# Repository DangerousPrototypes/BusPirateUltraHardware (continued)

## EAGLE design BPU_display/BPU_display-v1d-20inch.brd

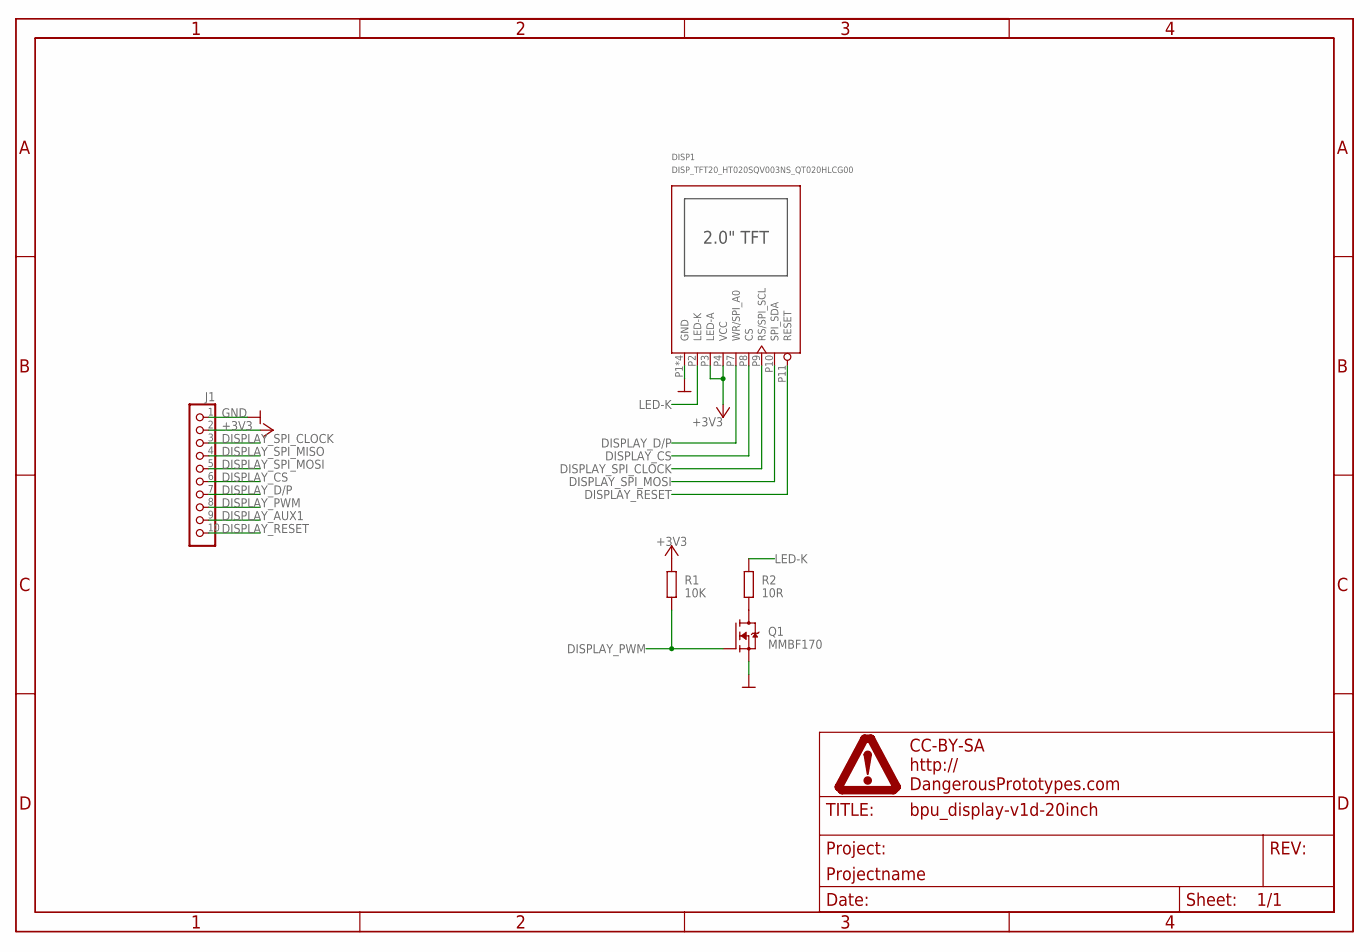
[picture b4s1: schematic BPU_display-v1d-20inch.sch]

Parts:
DISP1: DISP_TFT20_HT020SQV003NS_QT020HLCG00; HT020SQV003NS_QT020HLCG00
J1: CON-FPC_X05B20L10T; X05B20L10T
PAGE1: FRAME_DINA4_L; DP_LOGO
Q1: MMBF170; SOT-23
R1: 10K; R0603
R2: 10R; R0603

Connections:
+3V3: DISP1.P3 (LED-A), DISP1.P4 (VCC), J1.2, R1.2
DISPLAY_AUX1: J1.9
DISPLAY_CS: DISP1.P8 (CS), J1.6
DISPLAY_D/P: DISP1.P7 (WR/SPI_A0), J1.7
DISPLAY_PWM: J1.8, Q1.1 (G), R1.1
DISPLAY_RESET: DISP1.P11 (RESET), J1.10
DISPLAY_SPI_CLOCK: DISP1.P9 (RS/SPI_SCL), J1.3
DISPLAY_SPI_MISO: J1.4
DISPLAY_SPI_MOSI: DISP1.P10 (SPI_SDA), J1.5
GND: DISP1.P1 (GND), DISP1.P5 (GND), DISP1.P6 (GND), DISP1.P12 (GND), J1.1, Q1.2 (S)
LED-K: DISP1.P2 (LED-K), R2.2
unnamed: Q1.3 (D), R2.1

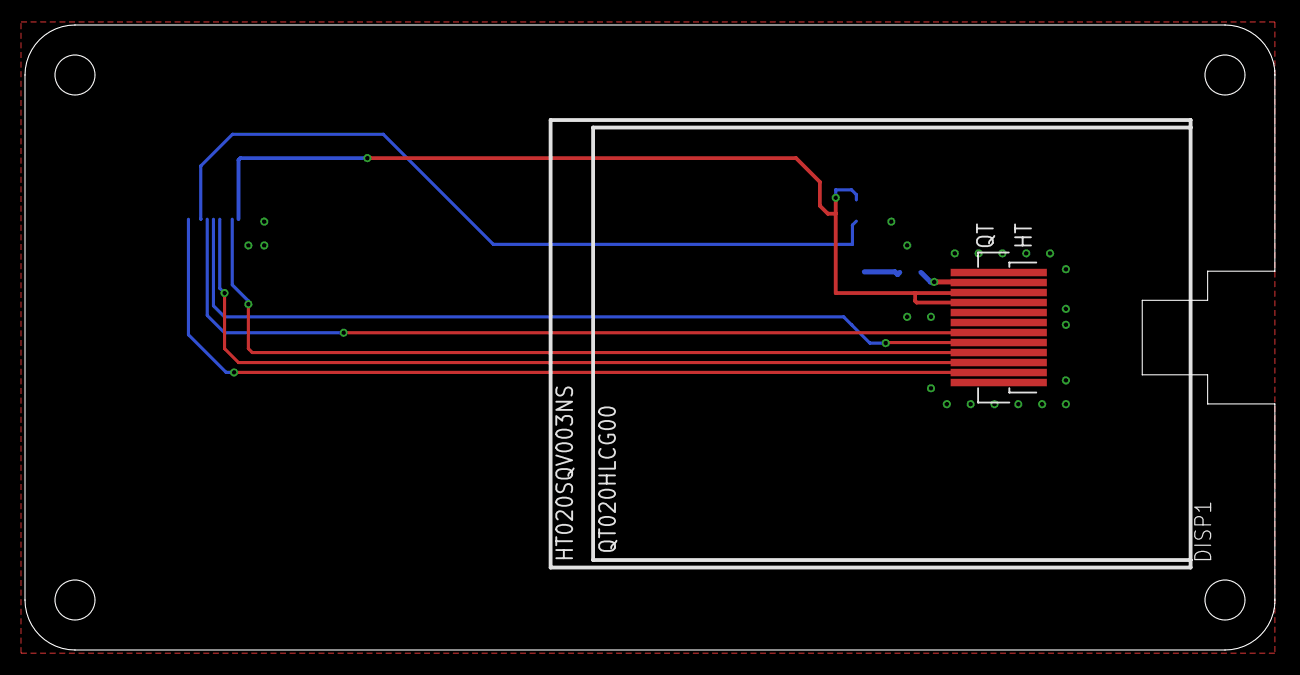
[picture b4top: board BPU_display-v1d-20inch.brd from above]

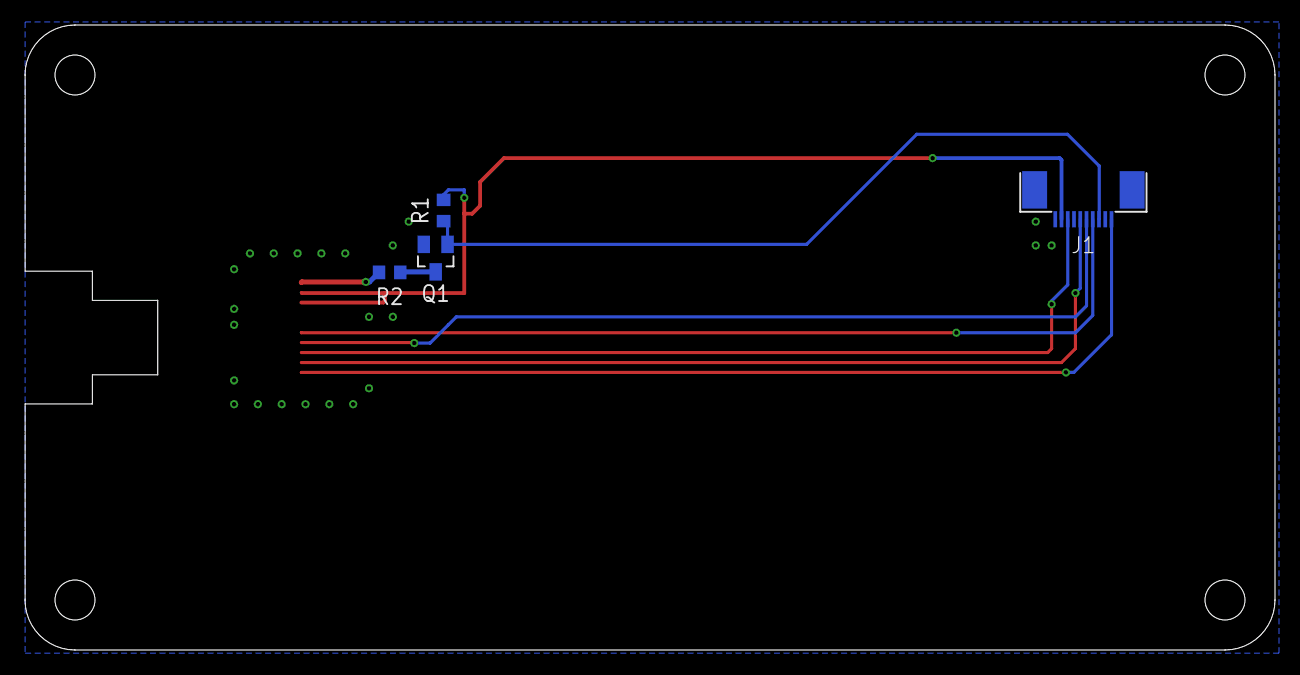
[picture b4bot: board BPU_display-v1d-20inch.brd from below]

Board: 2 copper layers, 100.0 x 50.0 mm, 6 parts (4 on the bottom side), 10 nets.

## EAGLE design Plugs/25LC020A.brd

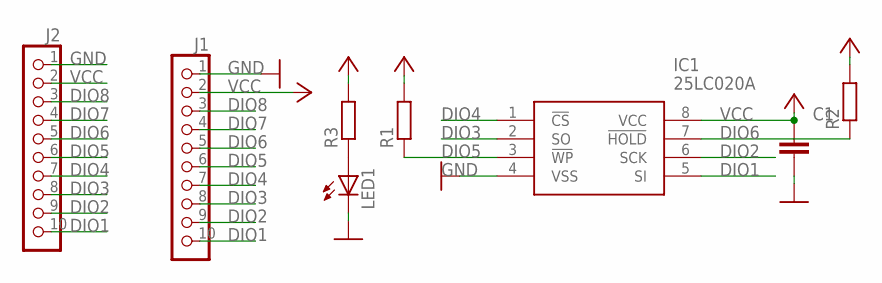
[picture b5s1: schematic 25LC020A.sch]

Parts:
C1: CAPACITOR_NPOL-0603; C603
IC1: 25LC020A; SOIC127P600X175-8N
J1: CON_HEADER_1X10-RIGHT_ANGLED_PTH; M1X10_FEMALE_RIGHT_ANGLED_PTH
J2: CON_HEADER_1X10-PTH; M1X10
LED1: LED-0805; LED-805
R1, R2, R3: RESISTOR-0603; R603

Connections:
DIO1: IC1.5 (SI), J1.10, J2.10
DIO2: IC1.6 (SCK), J1.9, J2.9
DIO3: IC1.2 (SO), J1.8, J2.8
DIO4: IC1.1 (!CS), J1.7, J2.7
DIO5: IC1.3 (!WP), J1.6, J2.6, R1.1
DIO6: IC1.7 (!HOLD), J1.5, J2.5, R2.1
DIO7: J1.4, J2.4
DIO8: J1.3, J2.3
GND: C1.2, IC1.4 (VSS), J1.1, J2.1, LED1.C
unnamed: LED1.A, R3.1
VCC: C1.1, IC1.8 (VCC), J1.2, J2.2, R1.2, R2.2, R3.2

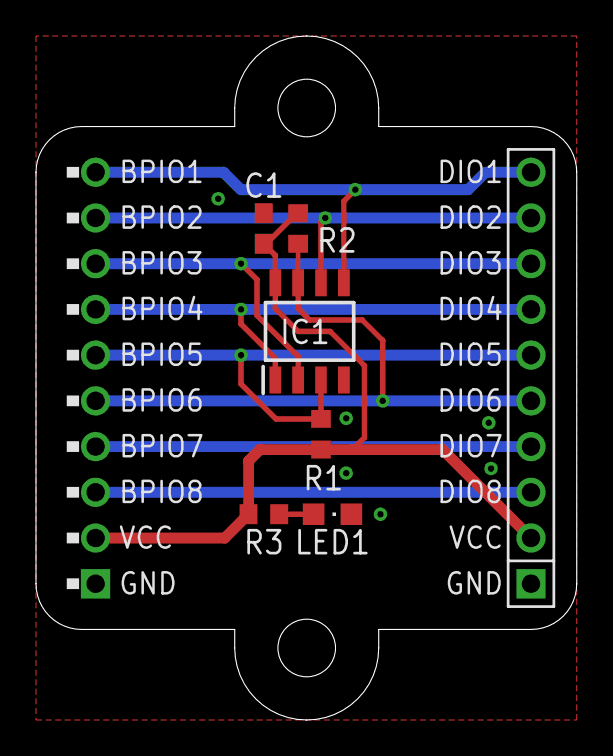
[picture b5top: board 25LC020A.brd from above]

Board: 2 copper layers, 30.0 x 38.0 mm, 8 parts (0 on the bottom side), 11 nets.

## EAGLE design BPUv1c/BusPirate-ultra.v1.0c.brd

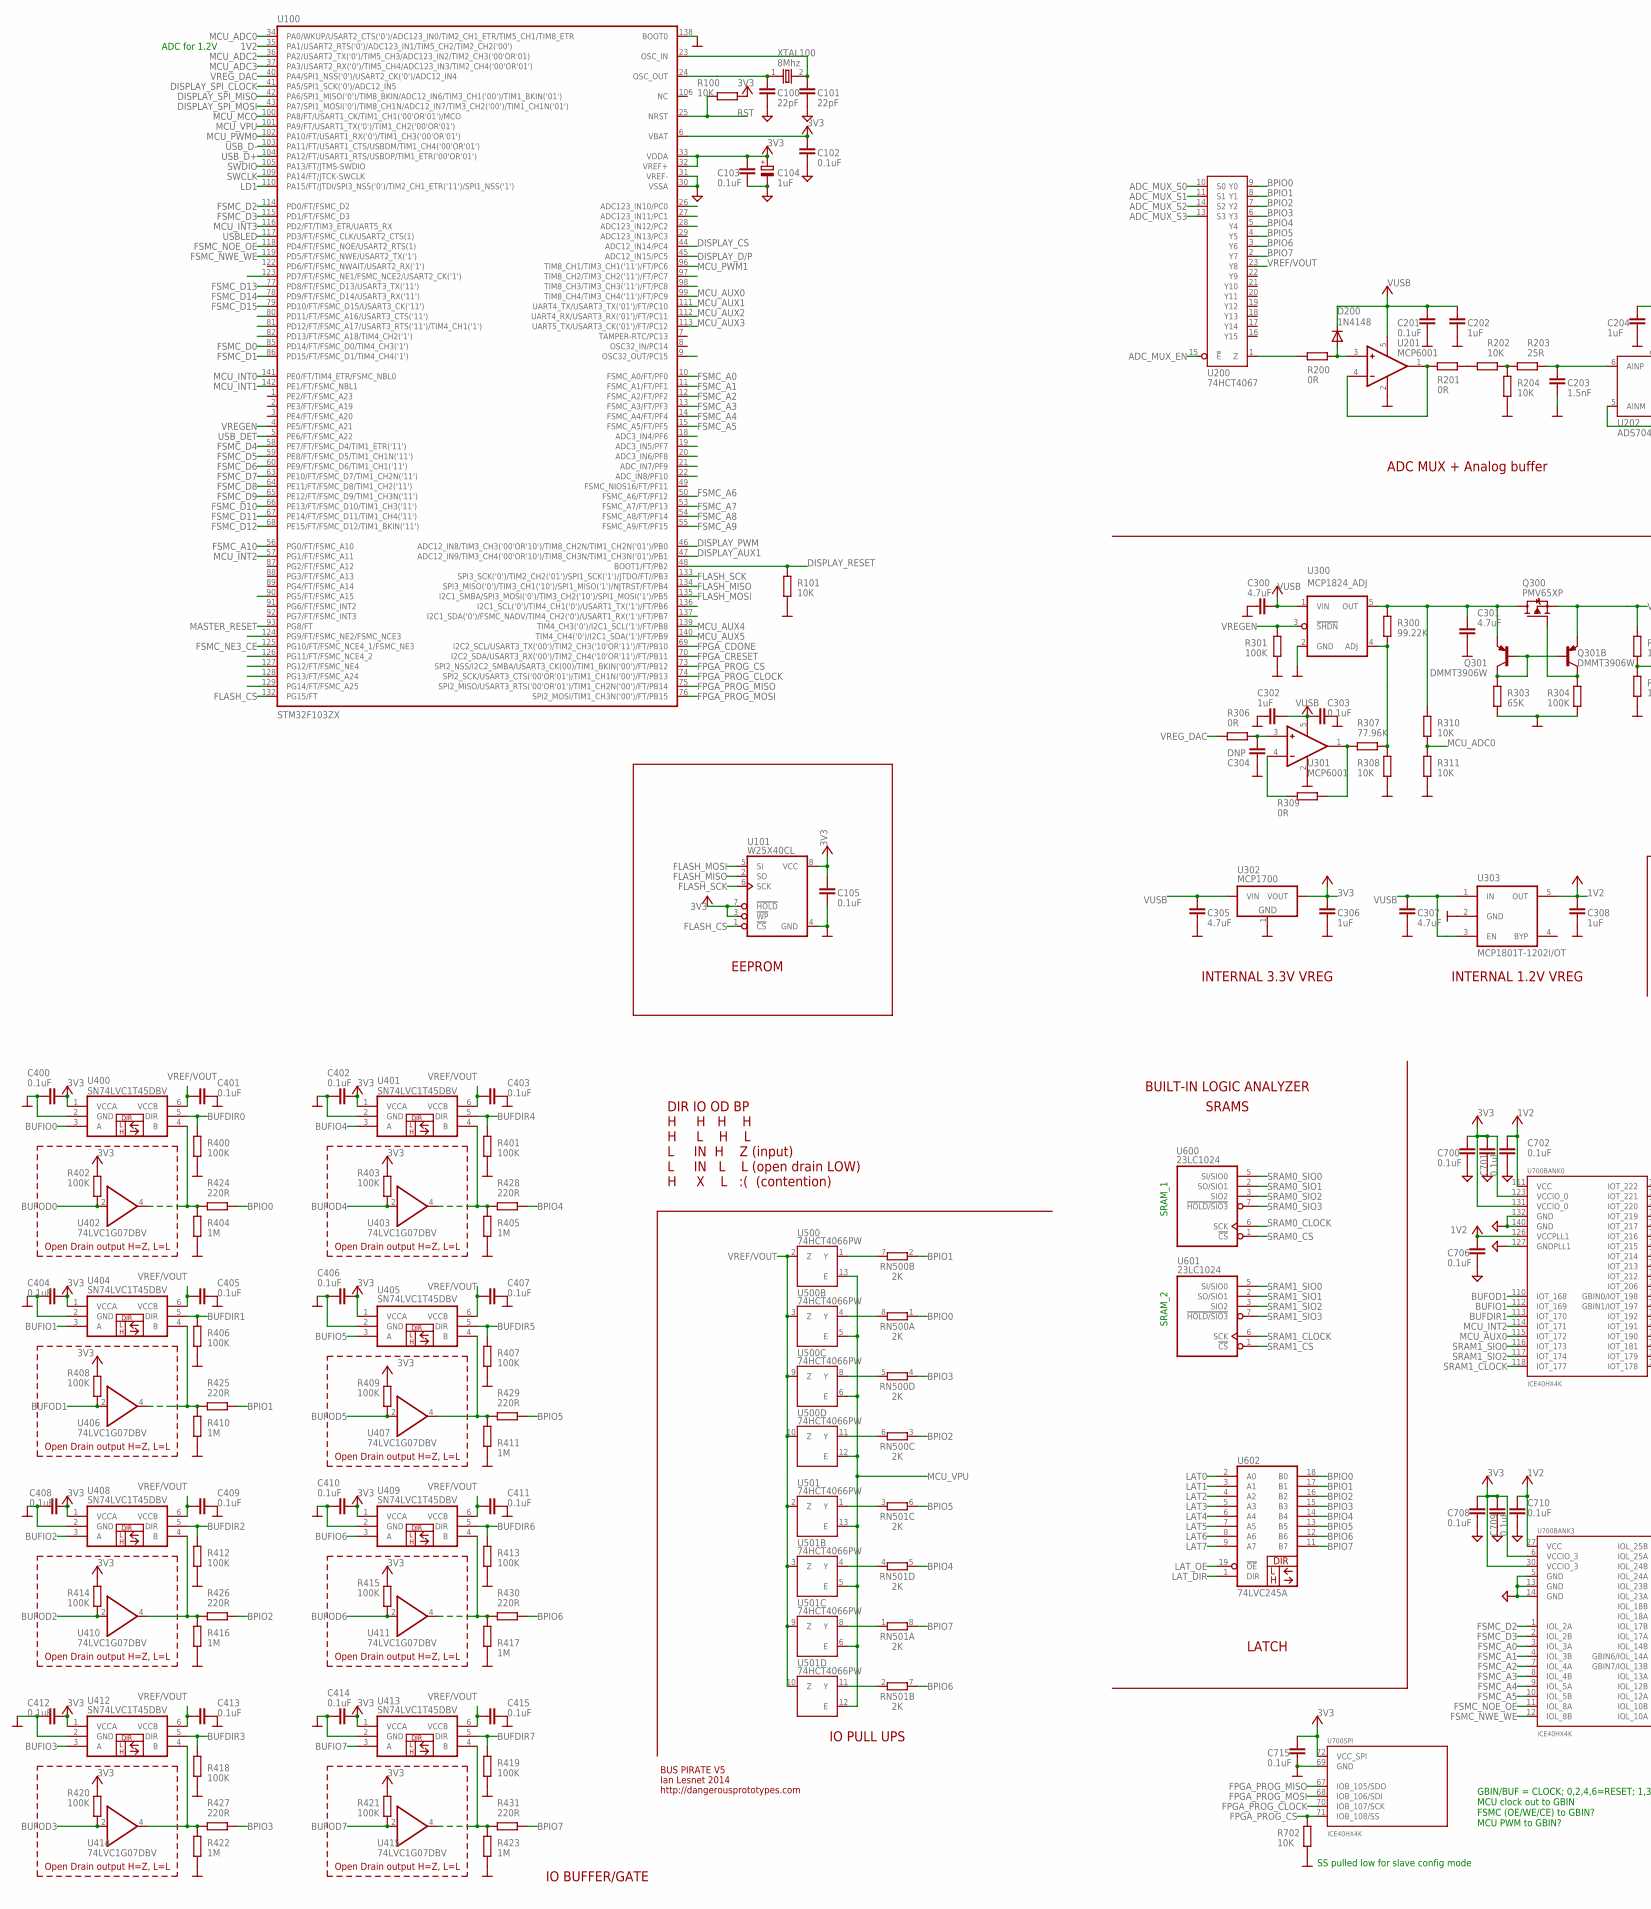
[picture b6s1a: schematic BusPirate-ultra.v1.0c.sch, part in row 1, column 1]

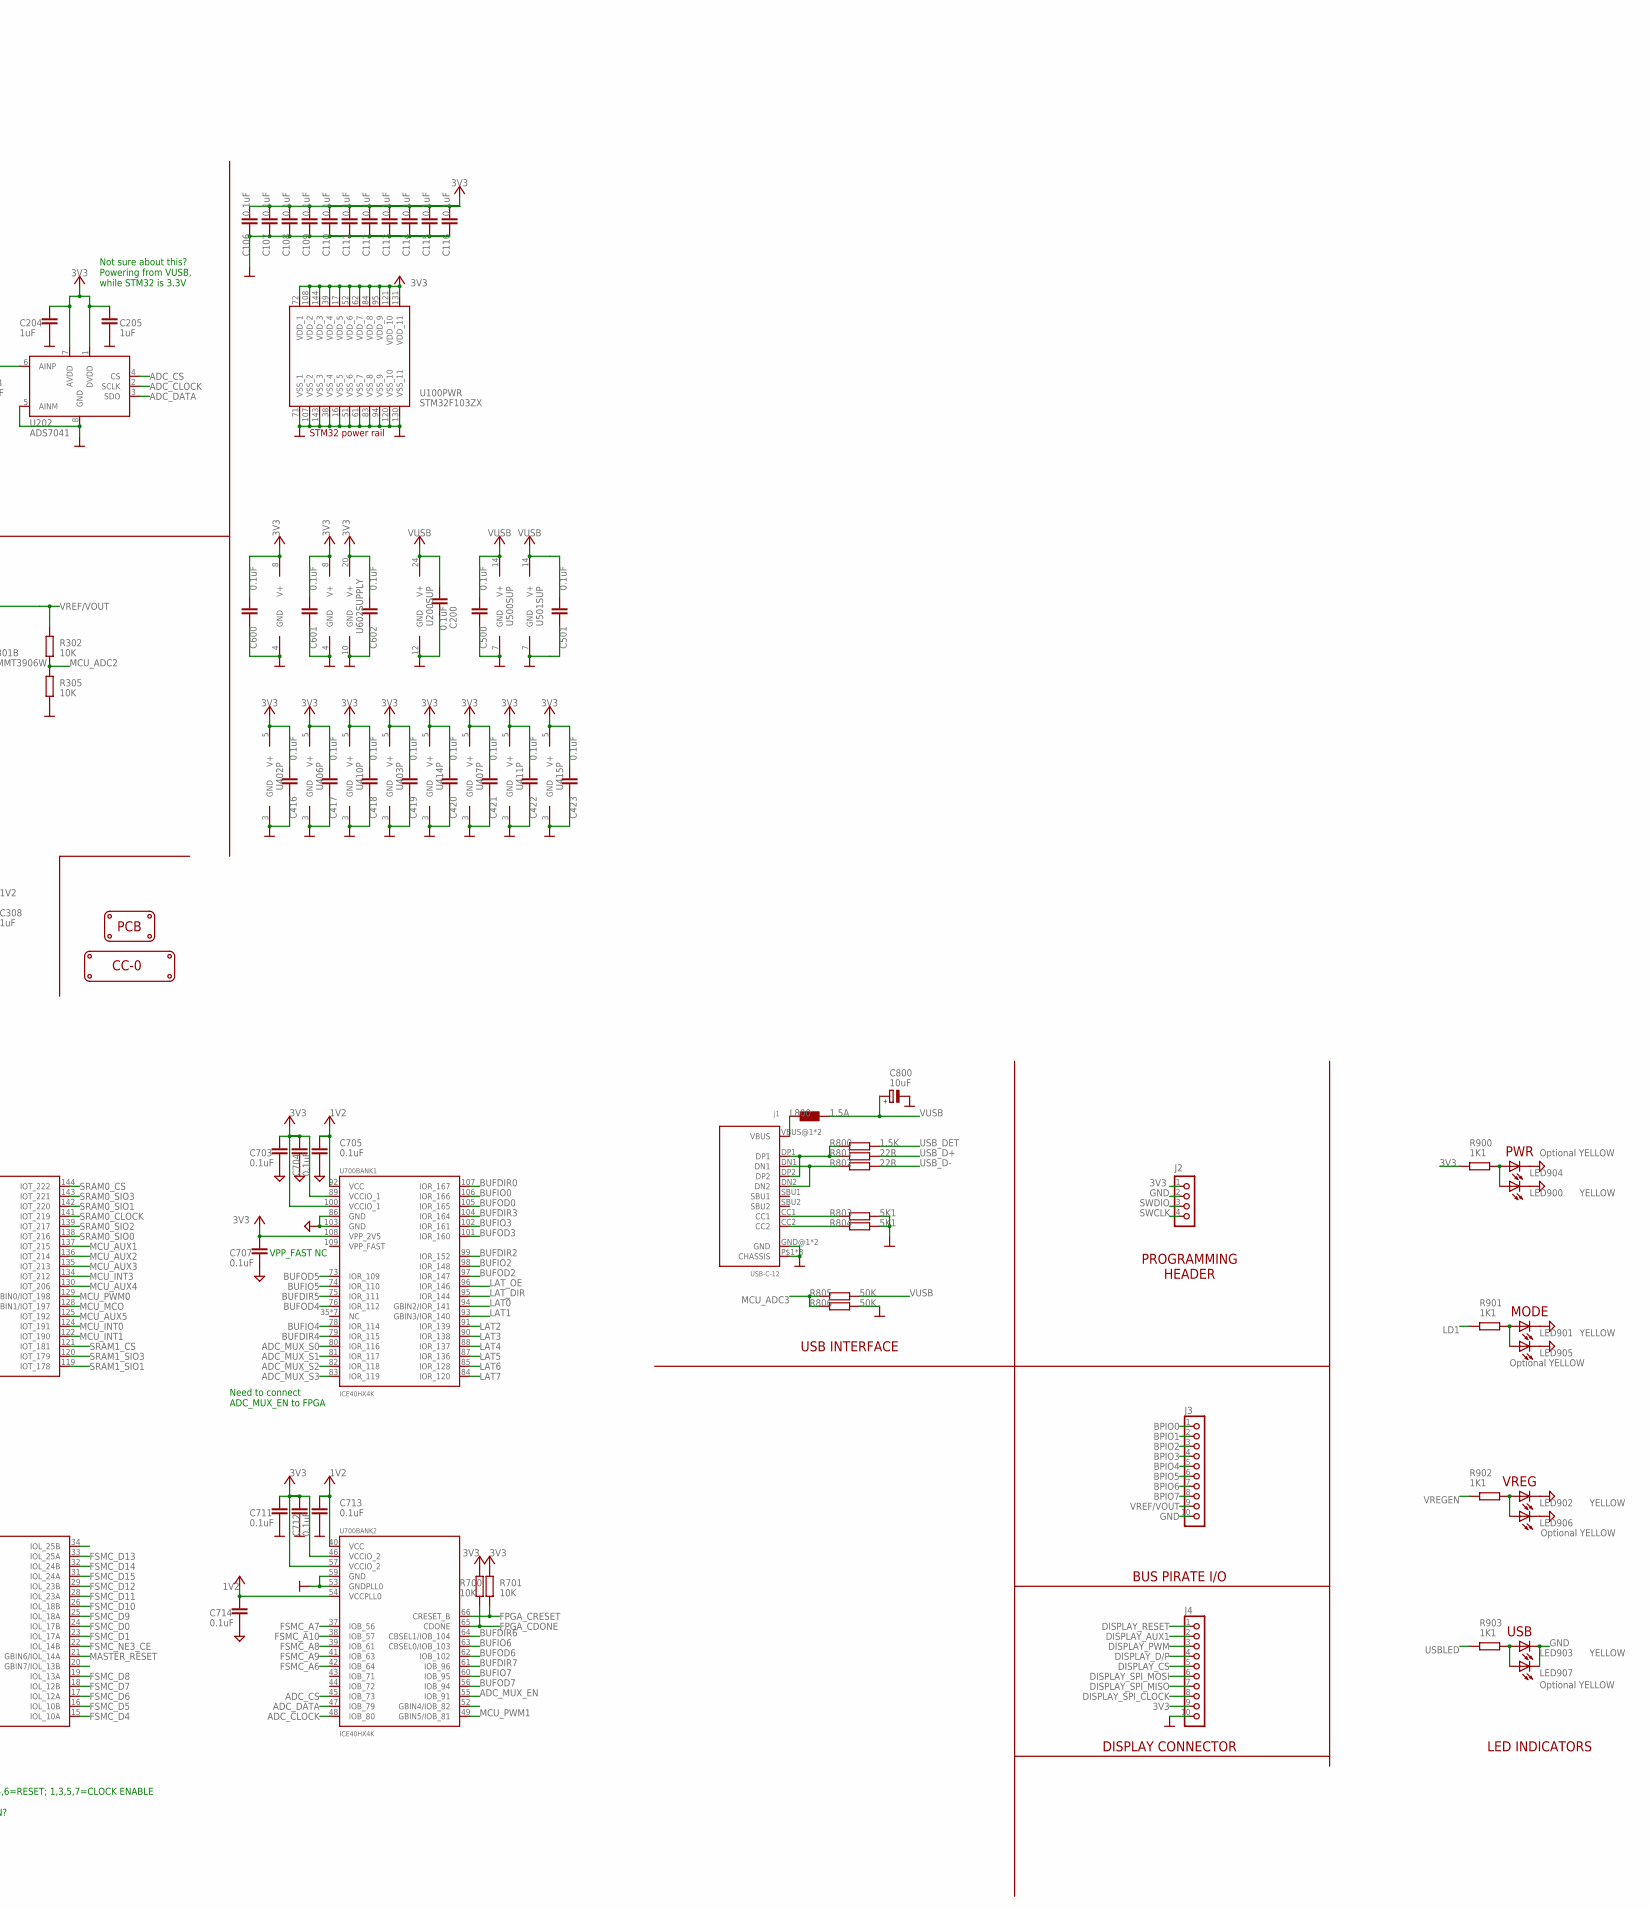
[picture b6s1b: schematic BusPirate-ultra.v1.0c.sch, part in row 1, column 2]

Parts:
C100, C101: 22pF; C402
C102, C103, C106, C108, C109, C110, C111, C112, C113, C114, C200, C201, C303, C400, C401, C402, C403, C404, C405, C406, C407, C408, C409, C410, C411, C412, C413, C414, C415, C416, C417, C418, C419, C420, C421, C422, C423, C501, C602, C702, C703, C704, C705, C707, C708, C709, C710, C711, C712, C713, C714, C715: 0.1uF; C402
C104: 1uF; SMC_A
C105, C107, C115, C116, C500, C600, C601, C700, C701, C706: 0.1uF; C603
C202, C204, C205, C302, C308: 1uF; C402
C203: 1.5nF; C402
C300, C301, C305, C307: 4.7uF; C603
C304: DNP; C603
C306: 1uF; C603
C800: 10uF; SMC_A
D200: 1N4148; SOD-123
J1: USB-C-12; C-31-M-12
J2: CON_HEADER_1X04; M1X4
J3: CON_HEADER_1X10-RIGHT_ANGLED_PTH_SHROUDED; M1X10_MALE_RIGHT_ANGLES_PTH_SHROUDED
J4: CON-FPC_X05B20L10T; X05B20L10T
L800: 1.5A; WE-KI_0805_B
LED900, LED901, LED902, LED903: YELLOW; LED-805
LED904, LED905, LED906, LED907: Optional YELLOW; LED-805
LOGO1: LOGO_CC-0
PCB1: PCB_DP_RECTANGLE-50X100; DP10050_V1
Q300: PMV65XP; SOT-23
Q301: DMMT3906W; SOT-363
R100, R101, R202, R204, R308, R310, R311, R700, R701, R702: 10K; R402
R200, R201, R309: 0R; R402
R203: 25R; R402
R300: 99.22K; R402
R301, R400, R401, R402, R403, R406, R407, R408, R409, R412, R413, R414, R415, R418, R419, R420, R421: 100K; R402
R302, R305: 10K; R603
R303: 65K; R603
R304: 100K; R603
R306: 0R; R603
R307: 77.96K; R402
R404, R405, R410, R411, R416, R417, R422, R423: 1M; R402
R424, R425, R426, R427, R428, R429, R430, R431: 220R; R402
R800: 1.5K; R402
R801, R802: 22R; R402
R803, R804: 5K1; R402
R805, R806: 50K; R402
R900, R901, R902, R903: 1K1; R603
RN500, RN501: 2K; RN8P-4R-CRA06S
U100: STM32F103ZX; TQFP-144
U101: W25X40CL; SOIC-8
U200: 74HCT4067; TSSOP-24
U201, U301: MCP6001; SOT-23-5
U202: ADS7041; VSSOP-8_DCU_PDSO_G8
U300: MCP1824_ADJ; SOT-23-5
U302: MCP1700; SOT-89
U303: MCP1801T-1202I/OT; SOT-23-5@1
U400, U401, U404, U405, U408, U409, U412, U413: SN74LVC1T45DBV; SC-70-6
U402, U403, U406, U407, U410, U411, U414, U415: 74LVC1G07DBV; SC-70-5
U500, U501: 74HCT4066PW; TSSOP-14
U600, U601: 23LC1024; SOIC-8
U602: 74LVC245A; TSSOP-20
U700: ICE40HX4K; TQFP-144
XTAL100: 8Mhz; XTAL_4X6

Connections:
1V2: C308.2, C702.1, C705.1, C706.1, C710.1, C713.1, C714.1, U100.35 (PA1/USART2_RTS('0')/ADC123_IN1/TIM5_CH2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), U303.5 (OUT), U700.27 (VCC), U700.40 (VCC), U700.54 (VCCPLL0), U700.92 (VCC), U700.111 (VCC), U700.126 (VCCPLL1)
3V3: C102.1, C103.1, C104.+, C105.1, C106.1, C107.1, C108.1, C109.1, C110.1, C111.1, C112.1, C113.1, C114.1, C115.1, C116.1, C204.1, C205.1, C306.2, C400.2, C402.2, C404.2, C406.2, C408.2, C410.2, C412.2, C414.2, C416.2, C417.2, C418.2, C419.2, C420.2, C421.2, C422.2, C423.2, C600.2, C601.2, C602.2, C700.1, C701.1, C703.1, C704.1, C707.1, C708.1, C709.1, C711.1, C712.1, C715.1, J2.1, J4.9, R100.2, R402.2, R403.2, R408.2, R409.2, R414.2, R415.2, R420.2, R421.2, R700.2, R701.2, R900.2, U100.6 (VBAT), U100.17 (VDD_5), U100.32 (VREF+), U100.33 (VDDA), U100.39 (VDD_4), U100.52 (VDD_6), U100.62 (VDD_7), U100.72 (VDD_1), U100.84 (VDD_8), U100.95 (VDD_9), U100.108 (VDD_2), U100.121 (VDD_10), U100.131 (VDD_11), U100.144 (VDD_3), U101.3 (!WP), U101.7 (!HOLD), U101.8 (VCC), U202.1 (DVDD), U202.7 (AVDD), U302.3 (VOUT), U400.1 (VCCA), U401.1 (VCCA), U402.5 (V+), U403.5 (V+), U404.1 (VCCA), U405.1 (VCCA), U406.5 (V+), U407.5 (V+), U408.1 (VCCA), U409.1 (VCCA), U410.5 (V+), U411.5 (V+), U412.1 (VCCA), U413.1 (VCCA), U414.5 (V+), U415.5 (V+), U600.8 (V+), U601.8 (V+), U602.20 (V+), U700.6 (VCCIO_3), U700.30 (VCCIO_3), U700.46 (VCCIO_2), U700.57 (VCCIO_2), U700.72 (VCC_SPI), U700.89 (VCCIO_1), U700.100 (VCCIO_1), U700.108 (VPP_2V5), U700.123 (VCCIO_0), U700.131 (VCCIO_0)
ADC_CLOCK: U202.2 (SCLK), U700.48 (IOB_80)
ADC_CS: U202.4 (CS), U700.45 (IOB_73)
ADC_DATA: U202.3 (SDO), U700.47 (IOB_79)
ADC_MUX_EN: U200.15 (!E), U700.55 (IOB_91)
ADC_MUX_S0: U200.10 (S0), U700.80 (IOR_116)
ADC_MUX_S1: U200.11 (S1), U700.81 (IOR_117)
ADC_MUX_S2: U200.14 (S2), U700.82 (IOR_118)
ADC_MUX_S3: U200.13 (S3), U700.83 (IOR_119)
BPIO0: J3.1, R424.1, RN500.1, U200.9 (Y0), U602.18 (B0)
BPIO0I: R404.2, R424.2, U400.4 (B), U402.4 (O)
BPIO1: J3.2, R425.1, RN500.2 (1), U200.8 (Y1), U602.17 (B1)
BPIO1I: R410.2, R425.2, U404.4 (B), U406.4 (O)
BPIO2: J3.3, R426.1, RN500.3 (1), U200.7 (Y2), U602.16 (B2)
BPIO2I: R416.2, R426.2, U408.4 (B), U410.4 (O)
BPIO3: J3.4, R427.1, RN500.4 (1), U200.6 (Y3), U602.15 (B3)
BPIO3I: R422.2, R427.2, U412.4 (B), U414.4 (O)
BPIO4: J3.5, R428.1, RN501.5 (2), U200.5 (Y4), U602.14 (B4)
BPIO4I: R405.2, R428.2, U401.4 (B), U403.4 (O)
BPIO5: J3.6, R429.1, RN501.6 (2), U200.4 (Y5), U602.13 (B5)
BPIO5I: R411.2, R429.2, U405.4 (B), U407.4 (O)
BPIO6: J3.7, R430.1, RN501.7 (2), U200.3 (Y6), U602.12 (B6)
BPIO6I: R417.2, R430.2, U409.4 (B), U411.4 (O)
BPIO7: J3.8, R431.1, RN501.8 (2), U200.2 (Y7), U602.11 (B7)
BPIO7I: R423.2, R431.2, U413.4 (B), U415.4 (O)
BUFDIR0: R400.2, U400.5 (DIR), U700.107 (IOR_167)
BUFDIR1: R406.2, U404.5 (DIR), U700.113 (IOT_170)
BUFDIR2: R412.2, U408.5 (DIR), U700.99 (IOR_152)
BUFDIR3: R418.2, U412.5 (DIR), U700.104 (IOR_164)
BUFDIR4: R401.2, U401.5 (DIR), U700.79 (IOR_115)
BUFDIR5: R407.2, U405.5 (DIR), U700.75 (IOR_111)
BUFDIR6: R413.2, U409.5 (DIR), U700.64 (CBSEL1/IOB_104)
BUFDIR7: R419.2, U413.5 (DIR), U700.61 (IOB_96)
BUFIO0: U400.3 (A), U700.106 (IOR_166)
BUFIO1: U404.3 (A), U700.112 (IOT_169)
BUFIO2: U408.3 (A), U700.98 (IOR_148)
BUFIO3: U412.3 (A), U700.102 (IOR_161)
BUFIO4: U401.3 (A), U700.78 (IOR_114)
BUFIO5: U405.3 (A), U700.74 (IOR_110)
BUFIO6: U409.3 (A), U700.63 (CBSEL0/IOB_103)
BUFIO7: U413.3 (A), U700.60 (IOB_95)
BUFOD0: R402.1, U402.2 (I), U700.105 (IOR_165)
BUFOD1: R408.1, U406.2 (I), U700.110 (IOT_168)
BUFOD2: R414.1, U410.2 (I), U700.97 (IOR_147)
BUFOD3: R420.1, U414.2 (I), U700.101 (IOR_160)
BUFOD4: R403.1, U403.2 (I), U700.76 (IOR_112)
BUFOD5: R409.1, U407.2 (I), U700.73 (IOR_109)
BUFOD6: R415.1, U411.2 (I), U700.62 (IOB_102)
BUFOD7: R421.1, U415.2 (I), U700.56 (IOB_94)
D+: J1.DP1, J1.DP2, R800.1, R801.2
D-: J1.DN1, J1.DN2, R802.2
DISPLAY_AUX1: J4.2, U100.47 (ADC12_IN9/TIM3_CH4('00'OR'10')/TIM8_CH3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)
DISPLAY_CS: J4.5, U100.44 (ADC12_IN14/PC4)
DISPLAY_D/P: J4.4, U100.45 (ADC12_IN15/PC5)
DISPLAY_PWM: J4.3, U100.46 (ADC12_IN8/TIM3_CH3('00'OR'10')/TIM8_CH2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)
DISPLAY_RESET: J4.1, R101.2, U100.48 (BOOT1/FT/PB2)
DISPLAY_SPI_CLOCK: J4.8, U100.41 (PA5/SPI1_SCK('0')/ADC12_IN5)
DISPLAY_SPI_MISO: J4.7, U100.42 (PA6/SPI1_MISO('0')/TIM8_BKIN/ADC12_IN6/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)
DISPLAY_SPI_MOSI: J4.6, U100.43 (PA7/SPI1_MOSI('0')/TIM8_CH1N/ADC12_IN7/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)
FLASH_CS: U100.132 (PG15/FT), U101.1 (!CS)
FLASH_MISO: U100.134 (SPI3_MISO('0')/TIM3_CH1('10')/SPI1_MISO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), U101.2 (SO)
FLASH_MOSI: U100.135 (I2C1_SMBA/SPI3_MOSI('0')/TIM3_CH2('10')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), U101.5 (SI)
FLASH_SCK: U100.133 (SPI3_SCK('0')/TIM2_CH2('01')/SPI1_SCK('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), U101.6 (SCK)
FPGA_CDONE: R700.1, U100.69 (I2C2_SCL/USART3_TX('00')/TIM2_CH3('10'O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), U700.65 (CDONE)
FPGA_CRESET: R701.1, U100.70 (I2C2_SDA/USART3_RX('00')/TIM2_CH4('10'O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), U700.66 (CRESET_B)
FPGA_PROG_CLOCK: U100.74 (SPI2_SCK/USART3_CTS('00'OR'01')/TIM1_CH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), U700.70 (IOB_107/SCK)
FPGA_PROG_CS: R702.2, U100.73 (SPI2_NSS/I2C2_SMBA/USART3_CK(00)/TIM1_B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), U700.71 (IOB_108/SS)
FPGA_PROG_MISO: U100.75 (SPI2_MISO/USART3_RTS('00'OR'01')/TIM1_C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), U700.67 (IOB_105/SDO)
FPGA_PROG_MOSI: U100.76 (SPI2_MOSI/TIM1_CH3N('00')/FT/PB15), U700.68 (IOB_106/SDI)
FSMC_A0: U100.10 (FSMC_A0/FT/PF0), U700.3 (IOL_3A)
FSMC_A1: U100.11 (FSMC_A1/FT/PF1), U700.4 (IOL_3B)
FSMC_A2: U100.12 (FSMC_A2/FT/PF2), U700.7 (IOL_4A)
FSMC_A3: U100.13 (FSMC_A3/FT/PF3), U700.8 (IOL_4B)
FSMC_A4: U100.14 (FSMC_A4/FT/PF4), U700.9 (IOL_5A)
FSMC_A5: U100.15 (FSMC_A5/FT/PF5), U700.10 (IOL_5B)
FSMC_A6: U100.50 (FSMC_A6/FT/PF12), U700.42 (IOB_64)
FSMC_A7: U100.53 (FSMC_A7/FT/PF13), U700.37 (IOB_56)
FSMC_A8: U100.54 (FSMC_A8/FT/PF14), U700.39 (IOB_61)
FSMC_A9: U100.55 (FSMC_A9/FT/PF15), U700.41 (IOB_63)
FSMC_A10: U100.56 (PG0/FT/FSMC_A10), U700.38 (IOB_57)
FSMC_D0: U100.85 (PD14/FT/FSMC_D0/TIM4_CH3('1')), U700.24 (IOL_17B)
FSMC_D1: U100.86 (PD15/FT/FSMC_D1/TIM4_CH4('1')), U700.23 (IOL_17A)
FSMC_D2: U100.114 (PD0/FT/FSMC_D2), U700.1 (IOL_2A)
FSMC_D3: U100.115 (PD1/FT/FSMC_D3), U700.2 (IOL_2B)
FSMC_D4: U100.58 (PE7/FT/FSMC_D4/TIM1_ETR('11')), U700.15 (IOL_10A)
FSMC_D5: U100.59 (PE8/FT/FSMC_D5/TIM1_CH1N('11')), U700.16 (IOL_10B)
FSMC_D6: U100.60 (PE9/FT/FSMC_D6/TIM1_CH1('11')), U700.17 (IOL_12A)
FSMC_D7: U100.63 (PE10/FT/FSMC_D7/TIM1_CH2N('11')), U700.18 (IOL_12B)
FSMC_D8: U100.64 (PE11/FT/FSMC_D8/TIM1_CH2('11')), U700.19 (IOL_13A)
FSMC_D9: U100.65 (PE12/FT/FSMC_D9/TIM1_CH3N('11')), U700.25 (IOL_18A)
FSMC_D10: U100.66 (PE13/FT/FSMC_D10/TIM1_CH3('11')), U700.26 (IOL_18B)
FSMC_D11: U100.67 (PE14/FT/FSMC_D11/TIM1_CH4('11')), U700.28 (IOL_23A)
FSMC_D12: U100.68 (PE15/FT/FSMC_D12/TIM1_BKIN('11')), U700.29 (IOL_23B)
FSMC_D13: U100.77 (PD8/FT/FSMC_D13/USART3_TX('11')), U700.33 (IOL_25A)
FSMC_D14: U100.78 (PD9/FT/FSMC_D14/USART3_RX('11')), U700.32 (IOL_24B)
FSMC_D15: U100.79 (PD10/FT/FSMC_D15/USART3_CK('11')), U700.31 (IOL_24A)
FSMC_NE3_CE: U100.125 (PG10/FT/FSMC_NCE4_1/FSMC_NE3), U700.22 (IOL_14B)
FSMC_NOE_OE: U100.118 (PD4/FT/FSMC_NOE/USART2_RTS(1)), U700.11 (IOL_8A)
FSMC_NWE_WE: U100.119 (PD5/FT/FSMC_NWE/USART2_TX('1')), U700.12 (IOL_8B)
GND: C100.2, C101.2, C102.2, C103.2, C104.-, C105.2, C106.2, C107.2, C108.2, C109.2, C110.2, C111.2, C112.2, C113.2, C114.2, C115.2, C116.2, C200.1, C201.2, C202.2, C203.2, C204.2, C205.2, C300.2, C301.2, C302.1, C303.1, C304.1, C305.1, C306.1, C307.1, C308.1, C400.1, C401.2, C402.1, C403.2, C404.1, C405.2, C406.1, C407.2, C408.1, C409.2, C410.1, C411.2, C412.1, C413.2, C414.1, C415.2, C416.1, C417.1, C418.1, C419.1, C420.1, C421.1, C422.1, C423.1, C500.1, C501.1, C600.1, C601.1, C602.1, C700.2, C701.2, C702.2, C703.2, C704.2, C705.2, C706.2, C707.2, C708.2, C709.2, C710.2, C711.2, C712.2, C713.2, C714.2, C715.2, C800.-, J1.GND@1 (GND), J1.GND@2 (GND), J1.P$1 (CHASSIS), J1.P$2 (CHASSIS), J1.P$3 (CHASSIS), J1.P$4 (CHASSIS), J1.P$5 (CHASSIS), J1.P$6 (CHASSIS), J1.P$7 (CHASSIS), J1.P$8 (CHASSIS), J2.2, J3.10, J4.10, LED900.C, LED901.C, LED902.C, LED903.C, LED904.C, LED905.C, LED906.C, LED907.C, R101.1, R204.2, R301.2, R303.1, R304.1, R305.2, R308.2, R311.2, R400.1, R401.1, R404.1, R405.1, R406.1, R407.1, R410.1, R411.1, R412.1, R413.1, R416.1, R417.1, R418.1, R419.1, R422.1, R423.1, R702.1, R803.2, R804.2, R806.1, U100.16 (VSS_5), U100.30 (VSSA), U100.31 (VREF-), U100.38 (VSS_4), U100.51 (VSS_6), U100.61 (VSS_7), U100.71 (VSS_1), U100.83 (VSS_8), U100.94 (VSS_9), U100.107 (VSS_2), U100.120 (VSS_10), U100.130 (VSS_11), U100.138 (BOOT0), U100.143 (VSS_3), U101.4 (GND), U200.12 (GND), U201.2 (V-), U202.5 (AINM), U202.8 (GND), U300.2 (GND), U301.2 (V-), U302.1 (GND), U303.2 (GND), U400.2 (GND), U401.2 (GND), U402.3 (GND), U403.3 (GND), U404.2 (GND), U405.2 (GND), U406.3 (GND), U407.3 (GND), U408.2 (GND), U409.2 (GND), U410.3 (GND), U411.3 (GND), U412.2 (GND), U413.2 (GND), U414.3 (GND), U415.3 (GND), U500.7 (GND), U501.7 (GND), U600.4 (GND), U601.4 (GND), U602.10 (GND), U700.5 (GND), U700.13 (GND), U700.14 (GND), U700.53 (GNDPLL0), U700.59 (GND), U700.69 (GND), U700.86 (GND), U700.103 (GND), U700.127 (GNDPLL1), U700.132 (GND), U700.140 (GND)
LAT0: U602.2 (A0), U700.94 (GBIN2/IOR_141)
LAT1: U602.3 (A1), U700.93 (GBIN3/IOR_140)
LAT2: U602.4 (A2), U700.91 (IOR_139)
LAT3: U602.5 (A3), U700.90 (IOR_138)
LAT4: U602.6 (A4), U700.88 (IOR_137)
LAT5: U602.7 (A5), U700.87 (IOR_136)
LAT6: U602.8 (A6), U700.85 (IOR_128)
LAT7: U602.9 (A7), U700.84 (IOR_120)
LAT_DIR: U602.1 (DIR), U700.95 (IOR_144)
LAT_OE: U602.19 (!OE), U700.96 (IOR_146)
LD1: R901.2, U100.110 (PA15/FT/JTDI/SPI3_NSS('0')/TIM2_CH1_ETR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)
MASTER_RESET: U100.93 (PG8/FT), U700.21 (GBIN6/IOL_14A)
MCU_ADC0: R310.2, R311.1, U100.34 (PA0/WKUP/USART2_CTS('0')/ADC123_IN0/TIM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)
MCU_ADC2: R302.2, R305.1, U100.36 (PA2/USART2_TX('0')/TIM5_CH3/ADC123_IN2/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)
MCU_ADC3: R805.2, R806.2, U100.37 (PA3/USART2_RX('0')/TIM5_CH4/ADC123_IN3/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)
MCU_AUX0: U100.99 (TIM8_CH4/TIM3_CH4('11')/FT/PC9), U700.115 (IOT_172)
MCU_AUX1: U100.111 (UART4_TX/USART3_TX('01')/FT/PC10), U700.137 (IOT_215)
MCU_AUX2: U100.112 (UART4_RX/USART3_RX('01')/FT/PC11), U700.136 (IOT_214)
MCU_AUX3: U100.113 (UART5_TX/USART3_CK('01')/FT/PC12), U700.135 (IOT_213)
MCU_AUX4: U100.139 (TIM4_CH3('0')/I2C1_SCL('1')/FT/PB8), U700.130 (IOT_206)
MCU_AUX5: U100.140 (TIM4_CH4('0')/I2C1_SDA('1')/FT/PB9), U700.125 (IOT_192)
MCU_INT0: U100.141 (PE0/FT/TIM4_ETR/FSMC_NBL0), U700.124 (IOT_191)
MCU_INT1: U100.142 (PE1/FT/FSMC_NBL1), U700.122 (IOT_190)
MCU_INT2: U100.57 (PG1/FT/FSMC_A11), U700.114 (IOT_171)
MCU_INT3: U100.116 (PD2/FT/TIM3_ETR/UART5_RX), U700.134 (IOT_212)
MCU_MCO: U100.100 (PA8/FT/USART1_CK/TIM1_CH1('00'OR'01')/M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), U700.128 (GBIN1/IOT_197)
MCU_PWM0: U100.102 (PA10/FT/USART1_RX('0')/TIM1_CH3('00'OR'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), U700.129 (GBIN0/IOT_198)
MCU_PWM1: U100.96 (TIM8_CH1/TIM3_CH1('11')/FT/PC6), U700.49 (GBIN5/IOB_81)
MCU_VPU: U100.101 (PA9/FT/USART1_TX('0')/TIM1_CH2('00'OR'0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), U500.5 (E), U500.6 (E), U500.12 (E), U500.13 (E), U501.5 (E), U501.6 (E), U501.12 (E), U501.13 (E)
unnamed: J1.VBUS@1 (VBUS), J1.VBUS@2 (VBUS), L800.2 (1)
unnamed: RN500.7 (2), U500.1 (Y)
unnamed: RN500.8 (2), U500.4 (Y)
unnamed: RN500.5 (2), U500.8 (Y)
unnamed: RN500.6 (2), U500.11 (Y)
unnamed: LED901.A, LED905.A, R901.1
unnamed: LED900.A, LED904.A, R900.1
unnamed: C101.1, U100.23 (OSC_IN), XTAL100.2
unnamed: C100.1, U100.24 (OSC_OUT), XTAL100.1
unnamed: Q300.1 (G), Q301.6 (C), R304.2
unnamed: R300.1, R307.2, R308.1, U300.4 (ADJ)
unnamed: LED903.A, LED907.A, R903.1
unnamed: J1.CC1, R803.1
unnamed: R309.1, U301.4 (-)
unnamed: LED902.A, LED906.A, R902.1
unnamed: J1.CC2, R804.1
unnamed: R201.2, R202.1
unnamed: R202.2, R203.1, R204.1
unnamed: R307.1, R309.2, U301.1 (OUT)
unnamed: C301.1, Q300.3 (D), Q301.4 (E), R300.2, R310.1, U300.5 (OUT)
unnamed: Q301.1 (B), Q301.2 (B), Q301.3 (C), R303.2
unnamed: C304.2, R306.2, U301.3 (+)
unnamed: D200.A, R200.2, U201.3 (+)
unnamed: RN501.3 (1), U501.1 (Y)
unnamed: RN501.4 (1), U501.4 (Y)
unnamed: RN501.1, U501.8 (Y)
unnamed: RN501.2 (1), U501.11 (Y)
unnamed: C203.1, R203.2, U202.6 (AINP)
unnamed: R200.1, U200.1 (Z)
unnamed: R201.1, U201.1 (OUT), U201.4 (-)
RST: R100.1, U100.25 (NRST)
SRAM0_CLOCK: U600.6 (SCK), U700.141 (IOT_219)
SRAM0_CS: U600.1 (!CS), U700.144 (IOT_222)
SRAM0_SIO0: U600.5 (SI/SIO0), U700.138 (IOT_216)
SRAM0_SIO1: U600.2 (SO/SIO1), U700.142 (IOT_220)
SRAM0_SIO2: U600.3 (SIO2), U700.139 (IOT_217)
SRAM0_SIO3: U600.7 (!HOLD/SIO3), U700.143 (IOT_221)
SRAM1_CLOCK: U601.6 (SCK), U700.118 (IOT_177)
SRAM1_CS: U601.1 (!CS), U700.121 (IOT_181)
SRAM1_SIO0: U601.5 (SI/SIO0), U700.116 (IOT_173)
SRAM1_SIO1: U601.2 (SO/SIO1), U700.119 (IOT_178)
SRAM1_SIO2: U601.3 (SIO2), U700.117 (IOT_174)
SRAM1_SIO3: U601.7 (!HOLD/SIO3), U700.120 (IOT_179)
SWCLK: J2.4, U100.109 (PA14/FT/JTCK-SWCLK)
SWDIO: J2.3, U100.105 (PA13/FT/JTMS-SWDIO)
USBLED: R903.2, U100.117 (PD3/FT/FSMC_CLK/USART2_CTS(1))
USB_D+: R801.1, U100.104 (PA12/FT/USART1_RTS/USBDP/TIM1_ETR('00'O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)
USB_D-: R802.1, U100.103 (PA11/FT/USART1_CTS/USBDM/TIM1_CH4('00'O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)
USB_DET: R800.2, U100.5 (PE6/FT/FSMC_A22)
VPP_FAST: U700.109 (VPP_FAST)
VREF/VOUT: C401.1, C403.1, C405.1, C407.1, C409.1, C411.1, C413.1, C415.1, J3.9, Q300.2 (S), Q301.5 (E), R302.1, U200.23 (Y8), U400.6 (VCCB), U401.6 (VCCB), U404.6 (VCCB), U405.6 (VCCB), U408.6 (VCCB), U409.6 (VCCB), U412.6 (VCCB), U413.6 (VCCB), U500.2 (Z), U500.3 (Z), U500.9 (Z), U500.10 (Z), U501.2 (Z), U501.3 (Z), U501.9 (Z), U501.10 (Z)
VREGEN: R301.1, R902.2, U100.4 (PE5/FT/FSMC_A21), U300.3 (!SHDN)
VREG_DAC: R306.1, U100.40 (PA4/SPI1_NSS('0')/USART2_CK('0')/ADC12_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)
VUSB: C200.2, C201.1, C202.1, C300.1, C302.2, C303.2, C305.2, C307.2, C500.2, C501.2, C800.+, D200.C, L800.1 (2), R805.1, U200.24 (V+), U201.5 (V+), U300.1 (VIN), U301.5 (V+), U302.2 (VIN), U303.1 (IN), U303.3 (EN), U500.14 (V+), U501.14 (V+)

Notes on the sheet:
BUS PIRATE V5
Ian Lesnet 2014
http://dangerousprototypes.com
SRAMS
IO BUFFER/GATE
BUS PIRATE I/O
PWR
MODE
VREG
PROGRAMMING HEADER
USB
INTERNAL 3.3V VREG
BUILT-IN LOGIC ANALYZER
ADC MUX + Analog buffer
USB INTERFACE
IO PULL UPS
LED INDICATORS
Open Drain output H=Z, L=L
SS pulled low for slave config mode
VPP_FAST NC
GBIN/BUF = CLOCK; 0,2,4,6=RESET; 1,3,5,7=CLOCK ENABLE MCU clock out to GBIN FSMC (OE/WE/CE) to GBIN? MCU PWM to GBIN?
DIR IO OD BP H H H H H L H L L IN H Z (input) L IN L L (open drain LOW) H X L :( (contention)
STM32 power rail
INTERNAL 1.2V VREG
SRAM_1
SRAM_2
EEPROM
LATCH
Not sure about this? Powering from VUSB, while STM32 is 3.3V
Need to connect ADC_MUX_EN to FPGA
ADC for 1.2V
DISPLAY CONNECTOR

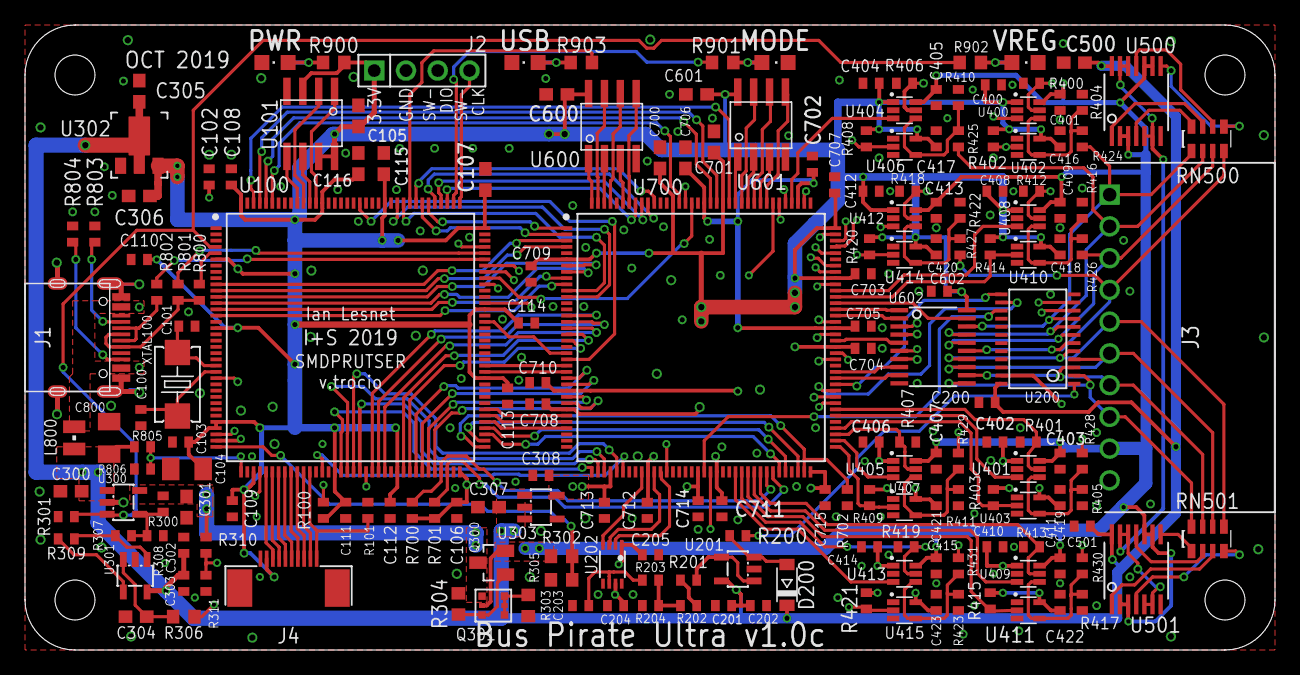
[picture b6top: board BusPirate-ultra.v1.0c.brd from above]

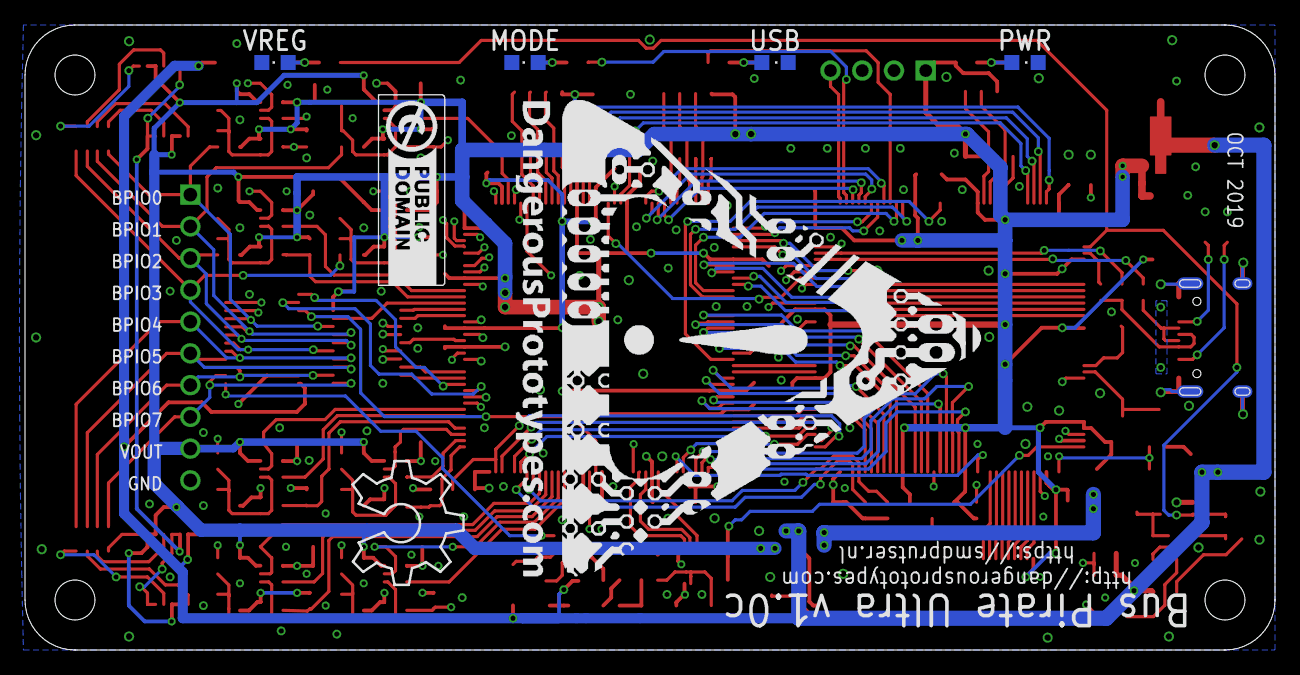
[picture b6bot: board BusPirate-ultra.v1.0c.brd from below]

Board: 4 copper layers, 100.0 x 50.0 mm, 198 parts (7 on the bottom side), 183 nets.

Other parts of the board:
U$1: DP-LOGO
U$2: OSHW_8X350_NOTEXT
U$4: DP_LOGO_ART_1.5X1.5
